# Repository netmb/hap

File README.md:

# This project is no longer maintained! We recommend esphome.io in combination with home-assistant.io as an alternative.
## If you build a lot of HAP-Actors like "HAP-Relais" and would like to continue using it: Use esphome.io with an ESP32 as an drop-in replacment. Works like charm!
Home Automation Project

HA using Atmel-AVR and Web 2.0.

Take a look at the [Wiki-Sites](https://github.com/netmb/hap/wiki) for more Information or if you want to jump-start, check the Installation-Instruction: [Installation](https://github.com/netmb/hap/wiki/Installation)

Some more documenation:

[HAP-CU-TechDok.pdf](https://github.com/netmb/hap/blob/master/doc/HAP-CU-TechDok.pdf?raw=true)

[Hap_QuickStart.pdf](https://github.com/netmb/hap/blob/master/doc/Hap_QuickStart.pdf?raw=true)

If you need support, check out: [hap-users group](https://groups.google.com/d/forum/hap-users)

This thread is also a good source: http://www.mikrocontroller.net/topic/148340#new

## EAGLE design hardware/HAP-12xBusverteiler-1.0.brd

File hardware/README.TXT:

Parts list:

HAP-ControlUnit-3.0: 
http://www.reichelt.de/?ACTION=20;AWKID=64257;PROVID=2084

Required Voltage-Regulator:
http://www.csd-electronics.de Part-Nr.: 2229 (LF50CDT)

HAP-ControlUnit-DIL-3.0:
http://www.reichelt.de/?;ACTION=20;LA=5010;AWKID=139808;PROVID=2084

Required MCP2515 DIL-Version:
http://www.csd-electronics.de Part-Nr.: 30486 (MCP2515-I/P)

HAP-USB-3.0: 
http://www.reichelt.de/?ACTION=20;AWKID=17196;PROVID=2084

HAP-LCD-1.0: 
http://www.reichelt.de/?ACTION=20;AWKID=8974;PROVID=2084

HAP-ZCD-3.0: 
http://www.reichelt.de/?ACTION=20;AWKID=8070;PROVID=2084

HAP-CU-Hutschiene-3.0: 
http://www.reichelt.de/?ACTION=20;AWKID=8056;PROVID=2084

HAP-5xMosFet-1.0: 
http://www.reichelt.de/?ACTION=20;AWKID=8055;PROVID=2084

HAP-5xDimmer-3.1: 
http://www.reichelt.de/?ACTION=20;AWKID=96183;PROVID=2084

HAP-6xRelais-3.1: 
https://secure.reichelt.de/index.html?;ACTION=20;AWKID=730469;PROVID=2084

HAP-4xJalousieaktor-1.0:
http://www.reichelt.de/?ACTION=20;AWKID=174350;PROVID=2084

HAP-4xPolwender-1.0:
http://www.reichelt.de/?ACTION=20;AWKID=174350;PROVID=2084

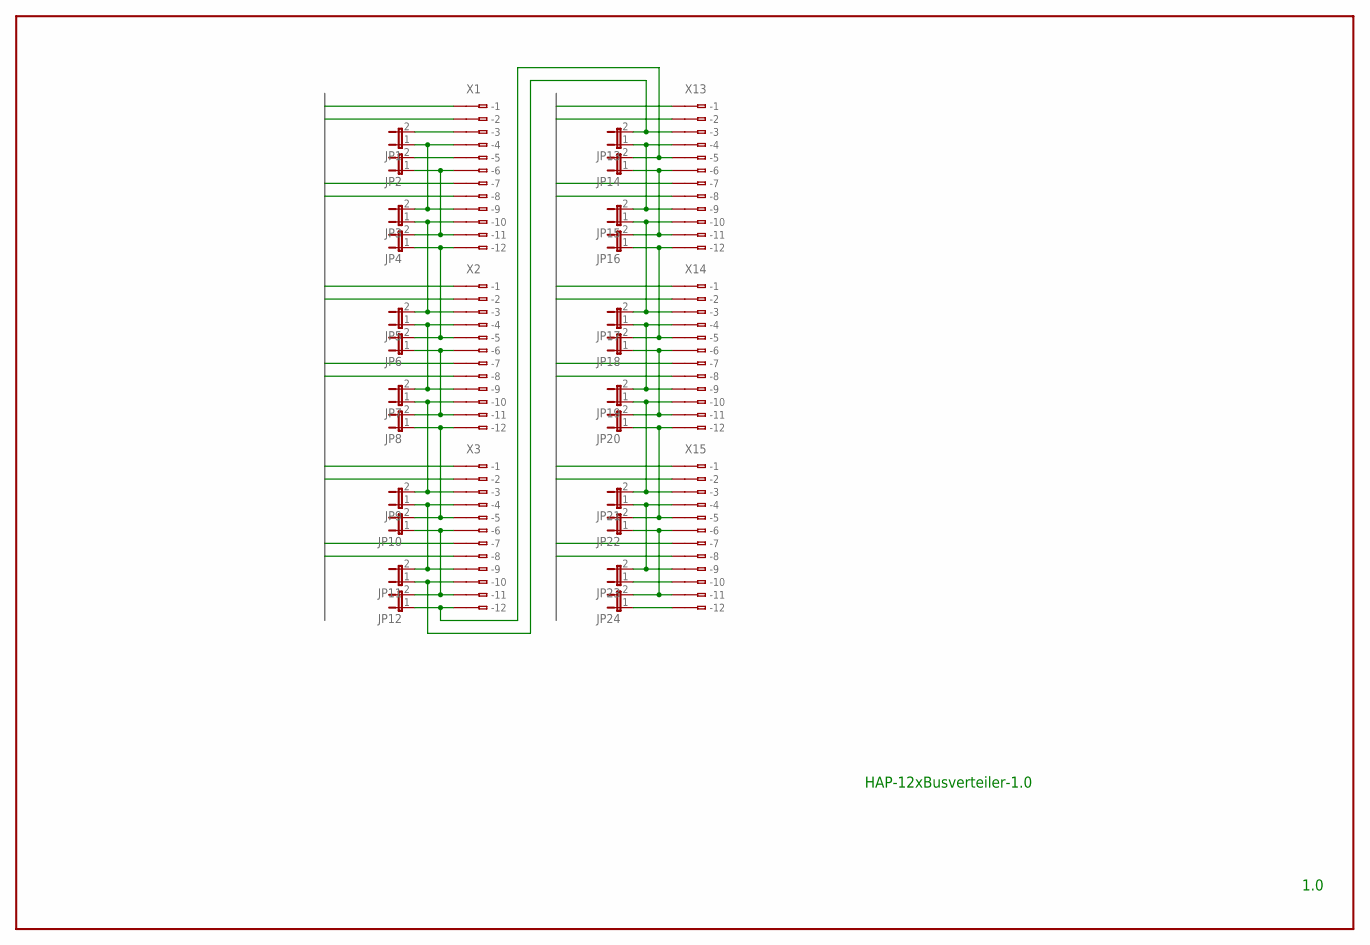
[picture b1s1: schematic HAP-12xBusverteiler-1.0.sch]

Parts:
JP1, JP2, JP3, JP4, JP5, JP6, JP7, JP8, JP9, JP10, JP11, JP12, JP13, JP14, JP15, JP16, JP17, JP18, JP19, JP20, JP21, JP22, JP23, JP24: JP1E; JP1
X1, X2, X3, X13, X14, X15: 233-512

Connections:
12V: X1.B1 (B-1), X1.B7 (B-7), X2.B1 (B-1), X2.B7 (B-7), X3.B1 (B-1), X3.B7 (B-7), X13.B1 (B-1), X13.B7 (B-7), X14.B1 (B-1), X14.B7 (B-7), X15.B1 (B-1), X15.B7 (B-7)
GND: X1.B2 (B-2), X1.B8 (B-8), X2.B2 (B-2), X2.B8 (B-8), X3.B2 (B-2), X3.B8 (B-8), X13.B2 (B-2), X13.B8 (B-8), X14.B2 (B-2), X14.B8 (B-8), X15.B2 (B-2), X15.B8 (B-8)
unnamed: JP1.1, JP3.2, X1.B4 (B-4), X1.B9 (B-9)
unnamed: JP3.1, JP5.2, X1.B10 (B-10), X2.B3 (B-3)
unnamed: JP5.1, JP7.2, X2.B4 (B-4), X2.B9 (B-9)
unnamed: JP13.1, JP15.2, X13.B4 (B-4), X13.B9 (B-9)
unnamed: JP14.1, JP16.2, X13.B6 (B-6), X13.B11 (B-11)
unnamed: JP15.1, JP17.2, X13.B10 (B-10), X14.B3 (B-3)
unnamed: JP16.1, JP18.2, X13.B12 (B-12), X14.B5 (B-5)
unnamed: JP2.1, JP4.2, X1.B6 (B-6), X1.B11 (B-11)
unnamed: JP4.1, JP6.2, X1.B12 (B-12), X2.B5 (B-5)
unnamed: JP6.1, JP8.2, X2.B6 (B-6), X2.B11 (B-11)
unnamed: JP7.1, JP9.2, X2.B10 (B-10), X3.B3 (B-3)
unnamed: JP17.1, JP19.2, X14.B4 (B-4), X14.B9 (B-9)
unnamed: JP18.1, JP20.2, X14.B6 (B-6), X14.B11 (B-11)
unnamed: JP19.1, JP21.2, X14.B10 (B-10), X15.B3 (B-3)
unnamed: JP1.2, X1.B3 (B-3)
unnamed: JP2.2, X1.B5 (B-5)
unnamed: JP20.1, JP22.2, X14.B12 (B-12), X15.B5 (B-5)
unnamed: JP21.1, JP23.2, X15.B4 (B-4), X15.B9 (B-9)
unnamed: JP8.1, JP10.2, X2.B12 (B-12), X3.B5 (B-5)
unnamed: JP9.1, JP11.2, X3.B4 (B-4), X3.B9 (B-9)
unnamed: JP22.1, JP24.2, X15.B6 (B-6), X15.B11 (B-11)
unnamed: JP10.1, JP12.2, X3.B6 (B-6), X3.B11 (B-11)
unnamed: JP11.1, JP13.2, X3.B10 (B-10), X13.B3 (B-3)
unnamed: JP23.1, X15.B10 (B-10)
unnamed: JP12.1, JP14.2, X3.B12 (B-12), X13.B5 (B-5)
unnamed: JP24.1, X15.B12 (B-12)

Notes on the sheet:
HAP-12xBusverteiler-1.0
1.0

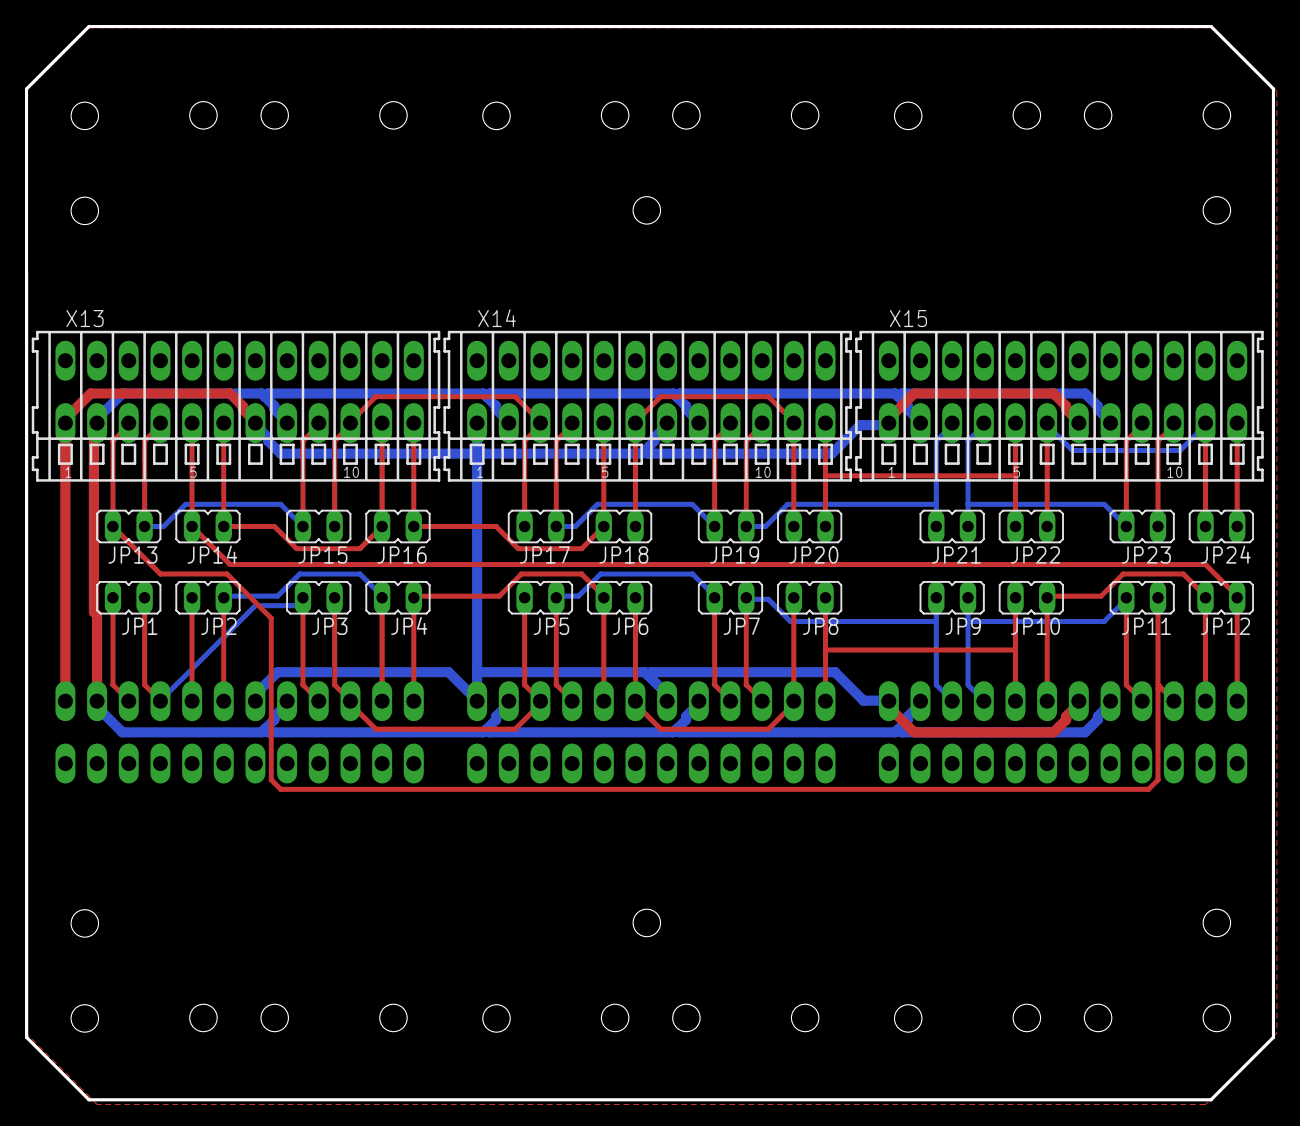
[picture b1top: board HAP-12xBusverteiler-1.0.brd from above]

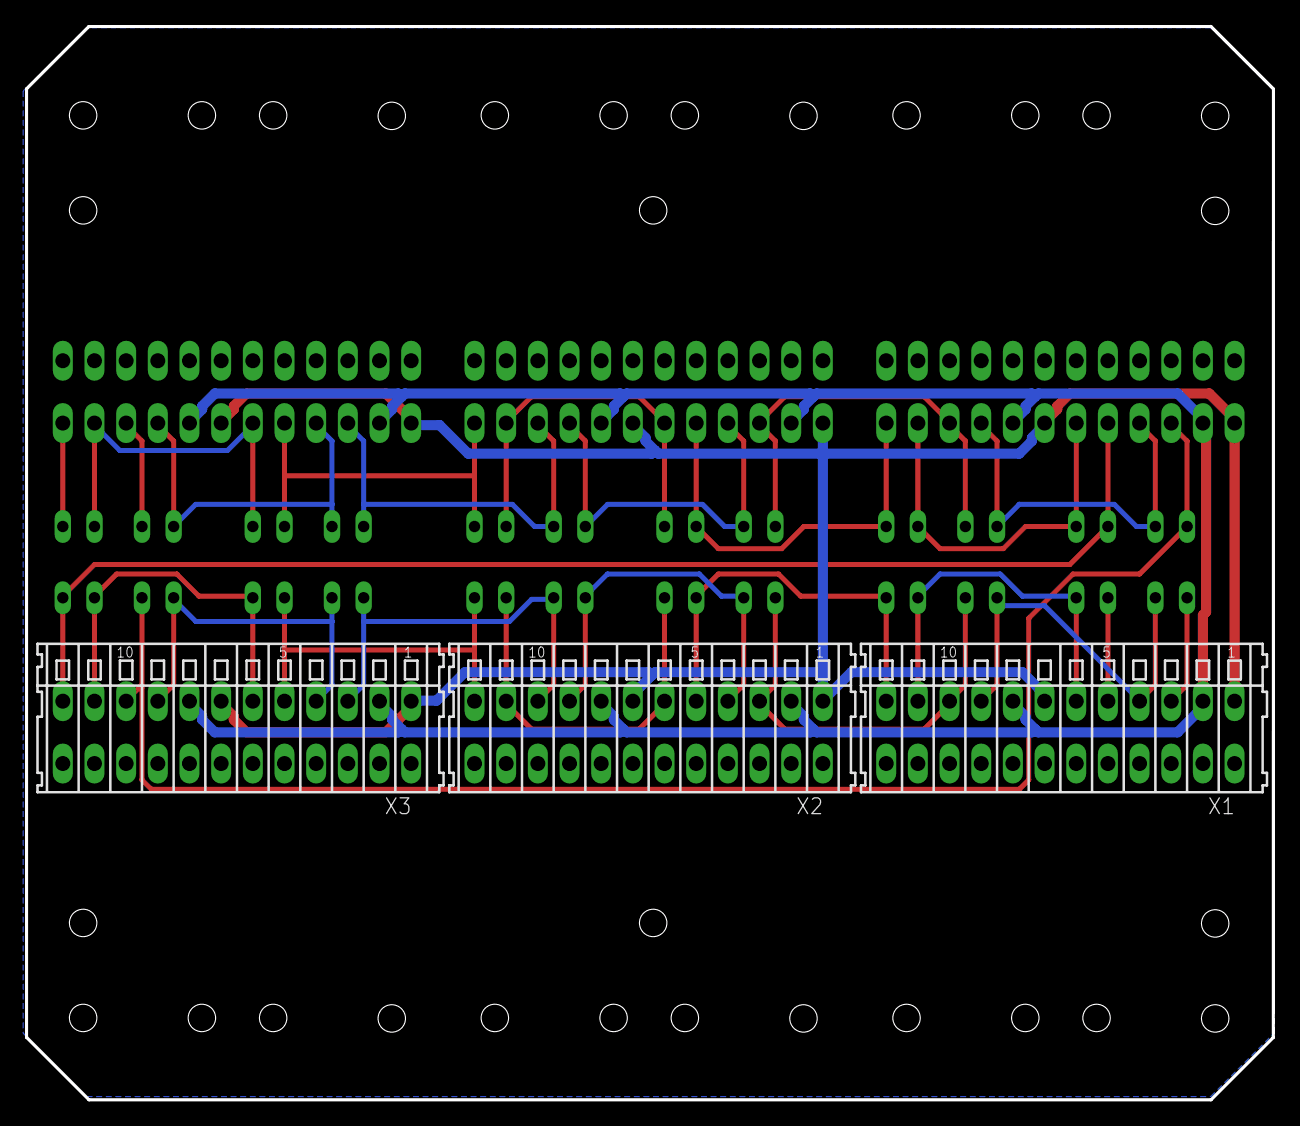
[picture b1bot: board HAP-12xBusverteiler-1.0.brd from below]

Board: 2 copper layers, 100.0 x 86.1 mm, 30 parts (3 on the bottom side), 28 nets.

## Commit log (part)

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2011-12-12 Edited wiki page AutonomeSteuerung through web user interface.
2011-12-12 Reedkontakt schaltet Ausgang
2011-12-12 Created wiki page through web user interface.
2011-12-12 Bewegungsmelder schaltet Ausgang mit Zeitverzögerung
2011-12-12 Deleted wiki page AufAbRollo through web user interface.
2011-12-12 Sicherheitsschaltung Dunstabzugshaube
2011-12-12 [Scheduler] Der Scheduler kann jetzt auch Makro-Scripts ausfuehren. Evt. bestehende Scheduler-Eintraege muessen aktualiesert werden.
2011-12-12 [Scheduler] komprimiertes Javascript nachgereicht.
2011-12-12 Heizstrahler mit Einschaltbegrenzung
2011-12-12 Zeit- und temperaturgesteuerte Warmwasser-Zirkulationspumpe
2011-12-12 [GUI] Macro Panel angepasst (bessere Verwendung in Verbindung mit dem Scheduler)
2011-12-14 Edited wiki page ScriptRollosNacht through web user interface.
2011-12-16 Die Helper-Scripte hap-sendcmd und hap-sendcmd2 senden jetzt 5 Retransmits, wenn eine Antwort ausbleibt. Das sollte bei instabilen Funk-Verbidungen helfen.
2011-12-16 Edited wiki page Scripting through web user interface.
2011-12-16 Bewegungsmelder für Beleuchtung nach Sonnenuntergang aktiv schalten
2011-12-18 Edited wiki page Menu through web user interface.
2011-12-18 Edited wiki page TecDoc through web user interface.
2011-12-18 Edited wiki page Backup through web user interface.
2011-12-19 Edited wiki page Subversion through web user interface.
2011-12-19 Verwendung des HAP-Scheduler
2011-12-19 Edited wiki page HAPScheduler through web user interface.
2011-12-19 Edited wiki page ScriptBrowserStart through web user interface.
2012-01-21 Added Bootloader-Sources.
2012-01-22 [Scheduler] Added fix hap-scheduler.pl-Version (thanks Nicolas)
2012-01-22 Added required base packages (deb)
2012-01-22 Edited wiki page Installation through web user interface.
2012-01-24 [Scheduler] Fixed hap-scheduler. Last version was badly broken.
2012-02-21 Edited wiki page USBVerbindungsueberwachnung through web user interface.
2012-09-17 'System Script Repo' added
2012-09-17 Edited wiki page SysScriptRepo through web user interface.
2012-09-17 Menü editiert
    * neue Kategorie "Konfiguration" für Inhalte die zur Konfiguration des HAP-Systems notwendig bzw. sinnvoll sind (Scheduler,...)
    * "System Scripts" als Überpunkt für alle Scripts die den HAP-Alltag erleichtern (Verbindungüberwachung,...)
    * "Scripting" als "Makros" angezeigt, damit der Bezug zur HAP Oberfläche klarer ist
2012-09-30 Edited wiki page EmailMessageOnMulticast through web user interface.
2012-10-03 moved [EmailMessageOnMulticast] link to existing "System Scripts" Repository
2012-10-25 Created branch Test.
2012-10-25 Test Branch für Erweiterungen
2012-10-29 Edited wiki page ErsteSchritte through web user interface.
2012-10-29 Beispiel-CCU
2012-10-29 upload
2013-01-29 Busverteiler Board
2013-01-29 Busverteiler Schema
2013-01-29 Removed file (wrong upload-path)
2013-02-19 Remove Deprecated-warnings (Authentication-Module, static-config-Part)
2013-02-24 Interim-update, please dont use.
2013-02-24 Re-added ext-Folder (new version 3.4)
2013-02-24 Edited wiki page Homematic through web user interface.
2013-03-03 Added Homematic window rotary handle sensor, push-button 2-channel surface mount, indoor motion-indicator Fixed some bugs in homematic-stuff Added GUI-Stuff for Makro-By-Datagram-stuff
2013-03-05 Added compressed Javascript-File
2013-03-09 Added Macro by datagram stuff
2013-03-09 Modified hap.sql
2013-03-09 Modified Homematic-Channel-Handling for Homematic-Devices with more than one channel
2013-03-11 Added missing ux-Directory. Thanks Erhard.
2013-03-18 Added Homematic-Config handling, extended Parser for Homematic-Config-handling
2013-03-24 Bild Warmwasser-Zirkulation 2
2013-03-24 Edited wiki page ASZirkulationspumpe2 through web user interface.
2013-03-24 Sensor-Zirkulation
2013-03-24 Added images for WIKI
2013-03-24 Removed link to old wiki
2013-03-24 Edited wiki page FunktionsweiseBootloader through web user interface.
2013-04-07 Changed Partlist for HAP-6xRelais
2013-05-20 Minor fixes
2013-11-07 Edited wiki page Basics through web user interface.
2013-11-07 Dimmer
2013-11-07 Adapter
2013-11-07 Jalousie
2013-11-07 Relai
2013-11-07 Edited wiki page DimmerStufe through web user interface.
2013-11-07 Edited wiki page RelaisStufe through web user interface.
2013-11-07 Edited wiki page Jalousieaktor through web user interface.
2013-11-07 Edited wiki page ControlUnit through web user interface.
2013-11-07 new size
2013-11-09 size
2013-11-10 Added Container-Layer to GUI-Types. This allows you to embed external HTML-Stuff in a DIV-Layer.
2013-11-10 Edited wiki page GUIContainer through web user interface.
2013-11-23 Added Homematic-Device HM-LC-Sw1-FM
2013-11-24 Changed Homematic-Config stuff handling (pushing commands via hap-cmd was unfinished)
2013-11-24 Edited wiki page HWLinks through web user interface.
2013-11-29 Edited wiki page DirektesLogin through web user interface.
2013-12-01 Added Homematic-Device HM-Sen-MDIR-O (Outdoor motion detector)
2013-12-01 Fixed small Bug in message handling
2013-12-01 Fixed hap.sql
2013-12-19 Edited wiki page WebcamPI through web user interface.
2013-12-21 Fixed some bugs V2 was not processed in dbStatusUpdate Login Redirect to relative url instead of full url
2013-12-21 Edited wiki page DS1820 through web user interface.
2014-01-16 Fixed bug in getFreeModuleAddress
2014-11-10 Added Homematic 4x Actor (PCB-Version)
2015-03-17 Migrating wiki contents from Google Code
2015-03-17 ./finishGoogleCodeGitHubWikiMigration: Moved ProjectHome.md from wiki branch to README.md in master branch.
2015-03-17 Create gh-pages branch via GitHub
2015-03-17 Added setup.sh-File
2015-03-17 Added Documentation
2015-03-21 adding of hap logo for front page
2015-03-26 Add small logo to front page
2016-11-12 if {"debug" : 1} is set in a terminal-session you will receive every state-change in this console-session. useful for interfacing with other systems.
2016-11-12 Added MQTT-Gateway-Daemon: Publishes every HAP-device-state as /hap/module/device/status You can change a device state by sending values to /hap/module/device Also added a script for creationg openha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
2016-11-12 Added .gitignore
2016-11-12 Added MQTT-Config-Parameters to hap.yml
2017-02-06 Added NodeJS HAP-MQTT-Gateway - replaces the perl-version
2017-05-01 updated mqtt gateway with shutter stop support removed restorable folders from mqtt gateway
2017-05-01 added node_modules to gitignore
2017-05-01 now really added support for stop
2017-09-27 Change Can-Bus-Speed from 10kbps to 125kbps
2017-09-27 Adapt Dimmer control to inverse behavior
2017-09-27 Change Can-Bus-Speed from 2.5.11 (Inverse Dimmer) to 125kbps
2017-09-27 Change Can-Bus-Speed from origin hap firmware 2.5.13 back to 10kbps
2017-09-27 Add new firmware 2.5.14 as clone from 2.5.13 with changed Can-Bus-Speed (10kbps->125kbps)
2017-09-27 Add firmware description
2017-09-27 Description rework
2017-09-27 Correct SVHAPhase in firmware 2.5.12 and 2.5.14
